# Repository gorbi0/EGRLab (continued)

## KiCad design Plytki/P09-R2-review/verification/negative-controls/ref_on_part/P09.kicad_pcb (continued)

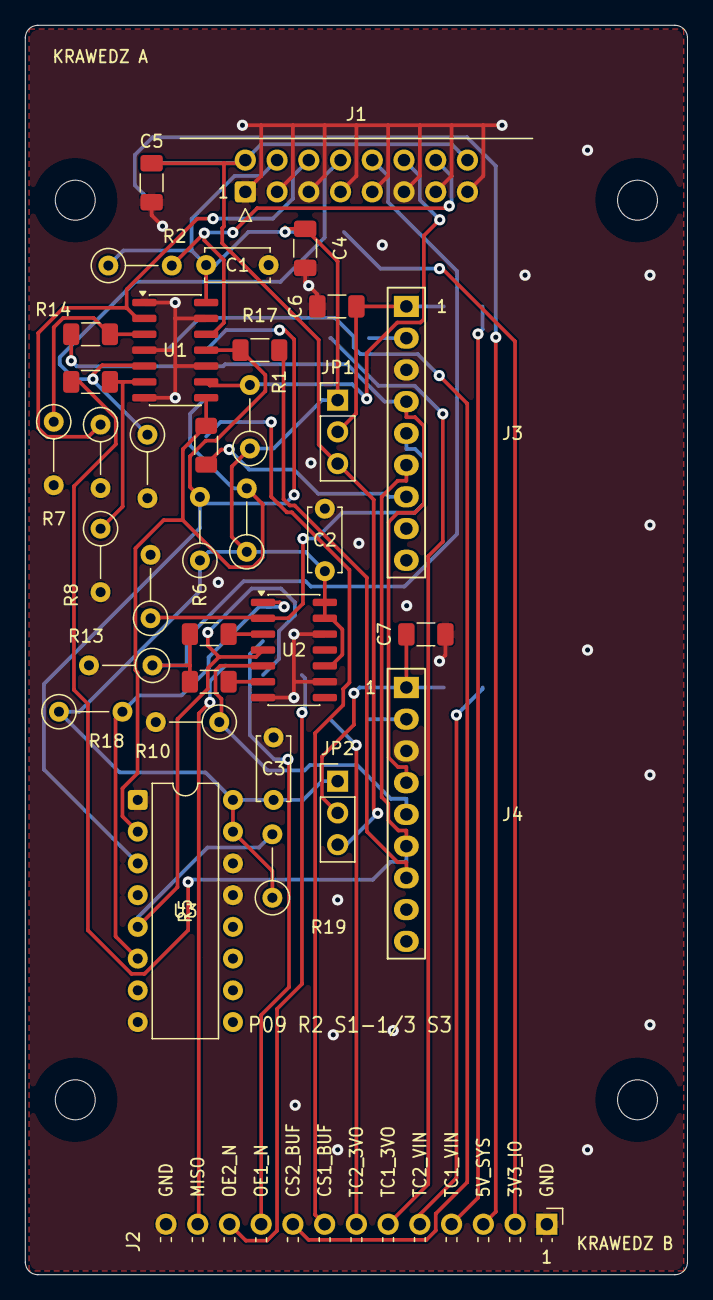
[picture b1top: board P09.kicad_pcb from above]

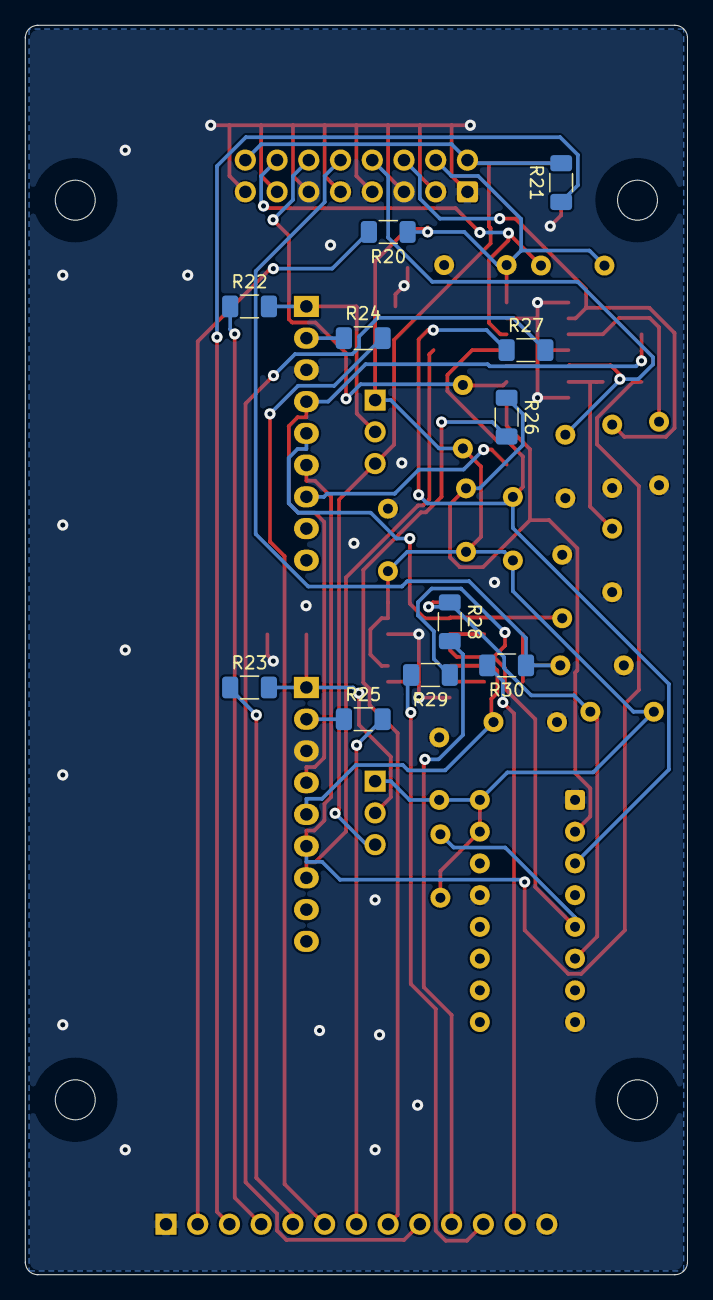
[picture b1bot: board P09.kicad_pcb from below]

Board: 2 copper layers, 53.0 x 100.0 mm, 50 parts (11 on the bottom side), 37 nets.

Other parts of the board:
H1, H2, H3, H4: M3 NPTH
